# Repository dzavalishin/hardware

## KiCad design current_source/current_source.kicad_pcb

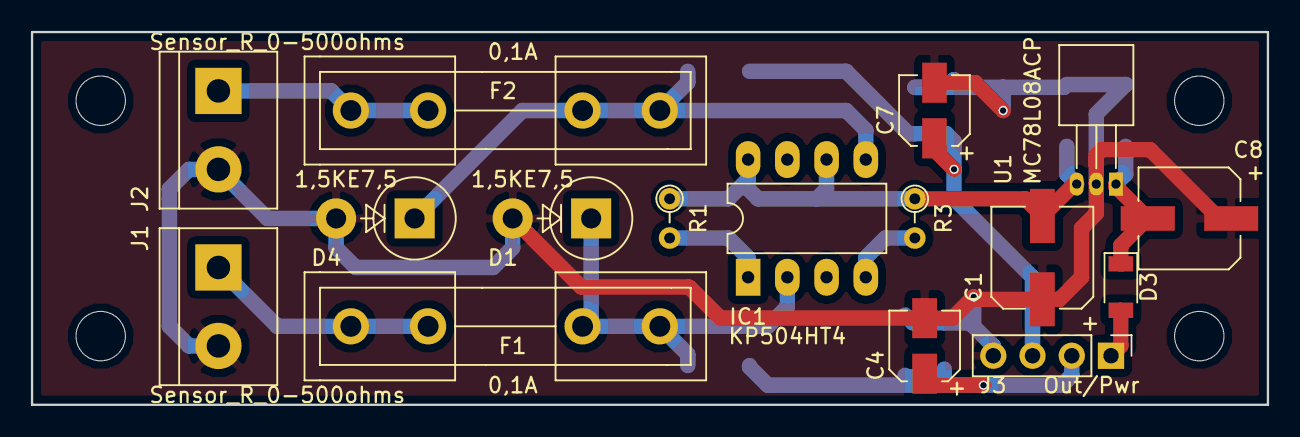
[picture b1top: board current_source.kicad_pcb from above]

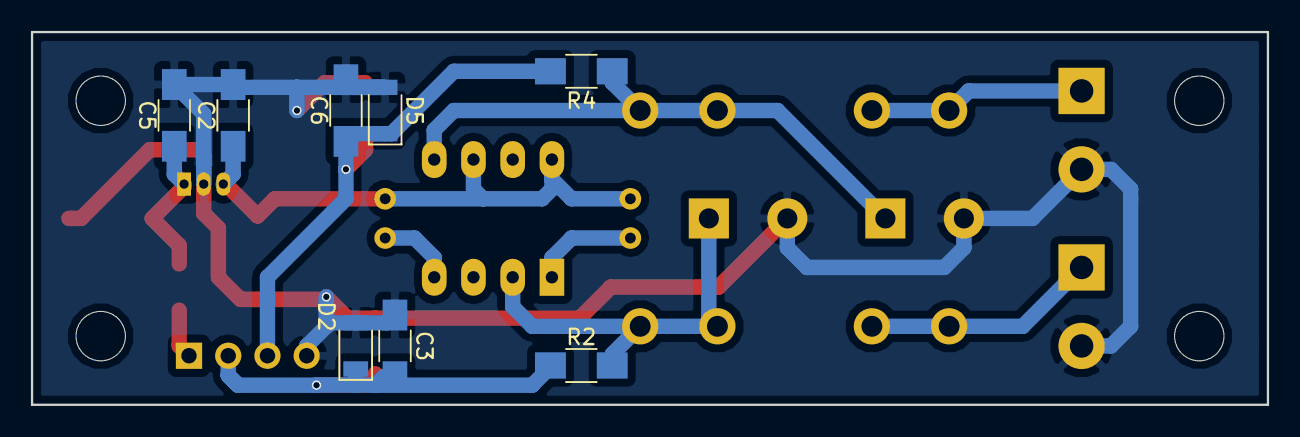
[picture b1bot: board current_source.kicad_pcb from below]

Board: 2 copper layers, 80.0 x 24.1 mm, 24 parts (8 on the bottom side), 12 nets.

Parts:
C1, C8: 100,0; CP_Elec_6.3x5.3
C2, C5: 0,33; C_1206_HandSoldering
C3, C6: 0,1; C_1206_HandSoldering
C4, C7: 10,0; CP_Elec_4x5.7
D1, D4: 1,5KE7,5; D_DO-201_P5.08mm_Vertical_AnodeUp
D2, D5: 4v7; D_1206
D3: 1n4148; D_1206
F1, F2: 0,1A; Fuseholder5x20_horiz_open_inline_Type-I
IC1: КР504НТ4; DIP-8_W7.62mm_LongPads
J1, J2: Sensor_R_0-500ohms; TerminalBlock_bornier-2_P5.08mm
J3: Out/Pwr; Pin_Header_Straight_1x04_Pitch2.54mm
R1, R3: 200 1%; R_Axial_DIN0204_L3.6mm_D1.6mm_P2.54mm_Vertical
R2, R4: 560; R_1206_HandSoldering
U1: MC78L08ACP; TO-92_Horizontal1_Inline_Narrow_Oval

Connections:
+8V: C1.2, C2.1, IC1.6, IC1.8, R1.1, R3.1, U1.3
+12V: D3.2, J3.1
/ADC_In_A: C3.1, C4.1, D2.1, J3.2, R2.1
/ADC_In_B: C6.1, C7.1, D5.1, J3.3, R4.1
GND: C1.1, C2.2, C3.2, C4.2, C5.2, C6.2, C7.2, C8.1, D1.2, D2.2, D4.2, D5.2, J1.2, J2.2, J3.4, U1.2
unnamed: C5.1, C8.2, D3.1, U1.1
unnamed: D1.1, F1.1, IC1.2, R2.2
unnamed: D4.1, F2.1, IC1.5, R4.2
unnamed: F1.2, J1.1
unnamed: F2.2, J2.1
unnamed: IC1.1, R1.2
unnamed: IC1.4, R3.2

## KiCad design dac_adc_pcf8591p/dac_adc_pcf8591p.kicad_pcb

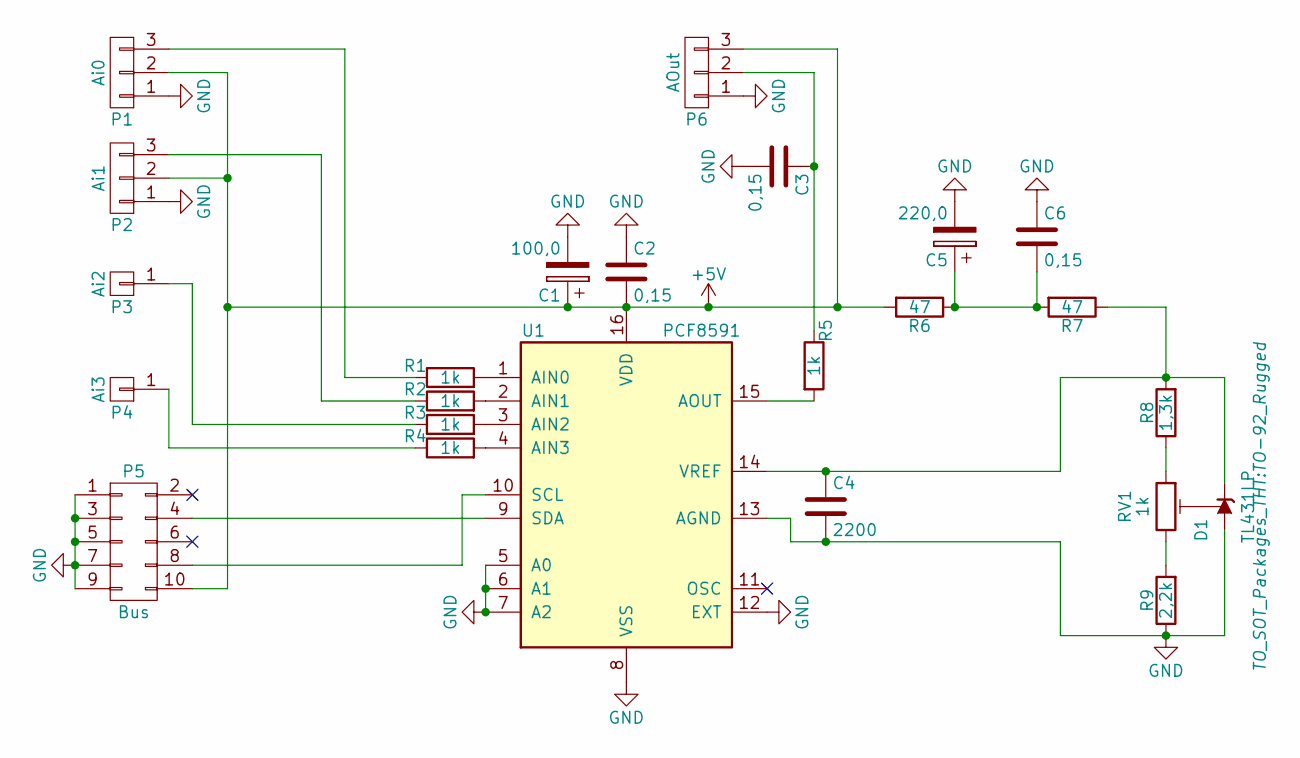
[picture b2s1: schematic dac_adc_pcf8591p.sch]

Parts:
C1: 100,0; CP_Tantalum_Case-B_EIA-3528-21_Hand
C2, C3, C6: 0,15; C_1206_HandSoldering
C4: 2200; C_1206_HandSoldering
C5: 220,0; CP_Tantalum_Case-B_EIA-3528-21_Hand
D1: TL431LP; TO-92_Rugged
P1: Ai0; Pin_Header_Straight_1x03_Pitch2.54mm
P2: Ai1; Pin_Header_Straight_1x03_Pitch2.54mm
P3: Ai2; Pin_Header_Straight_1x01_Pitch2.54mm
P4: Ai3; Pin_Header_Straight_1x01_Pitch2.54mm
P5: Bus; Pin_Header_Straight_2x05_Pitch2.54mm
P6: AOut; Pin_Header_Straight_1x03_Pitch2.54mm
R1, R2, R3, R4, R5: 1k; R_1206_HandSoldering
R6, R7: 47; R_1206_HandSoldering
R8: 1,3k; R_1206_HandSoldering
R9: 2,2k; R_1206_HandSoldering
RV1: 1k; Potentiometer_Trimmer_Bourns_3296W
U1: PCF8591; DIP-16_W7.62mm_LongPads

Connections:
+5V: C1.1, C2.2, P1.2, P2.2, P5.10, P6.3, R6.2, U1.16 (VDD)
GND: C1.2, C2.1, C3.2, C4.2, C5.2, C6.1, D1.2 (A), P1.1, P2.1, P5.1, P5.3, P5.5, P5.7, P5.9, P6.1, R9.1, U1.5 (A0), U1.6 (A1), U1.7 (A2), U1.8 (VSS), U1.12 (EXT), U1.13 (AGND)
unnamed: C3.1, P6.2, R5.1
unnamed: C4.1, D1.3 (K), R7.1, R8.2, U1.14 (VREF)
unnamed: C5.1, C6.2, R6.1, R7.2
unnamed: D1.1 (REF), RV1.2
unnamed: P1.3, R1.1
unnamed: P2.3, R2.1
unnamed: P3.1, R3.1
unnamed: P4.1, R4.1
unnamed: P5.4, U1.9 (SDA)
unnamed: P5.8, U1.10 (SCL)
unnamed: R1.2, U1.1 (AIN0)
unnamed: R2.2, U1.2 (AIN1)
unnamed: R3.2, U1.3 (AIN2)
unnamed: R4.2, U1.4 (AIN3)
unnamed: R5.2, U1.15 (AOUT)
unnamed: R8.1, RV1.1
unnamed: R9.2, RV1.3

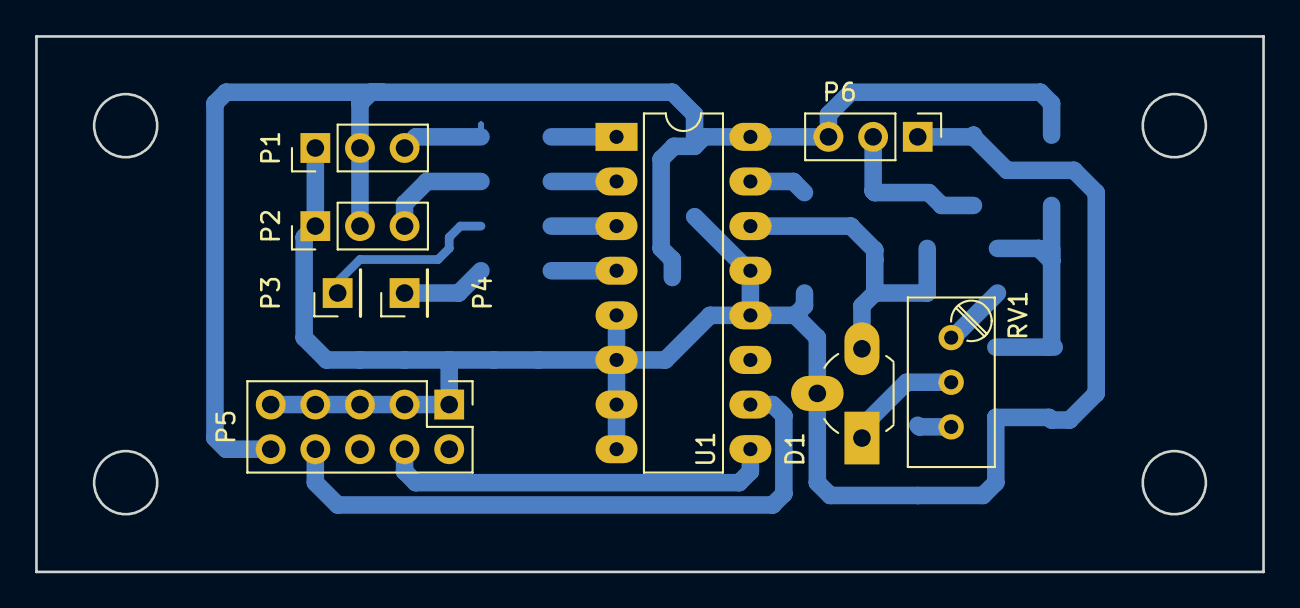
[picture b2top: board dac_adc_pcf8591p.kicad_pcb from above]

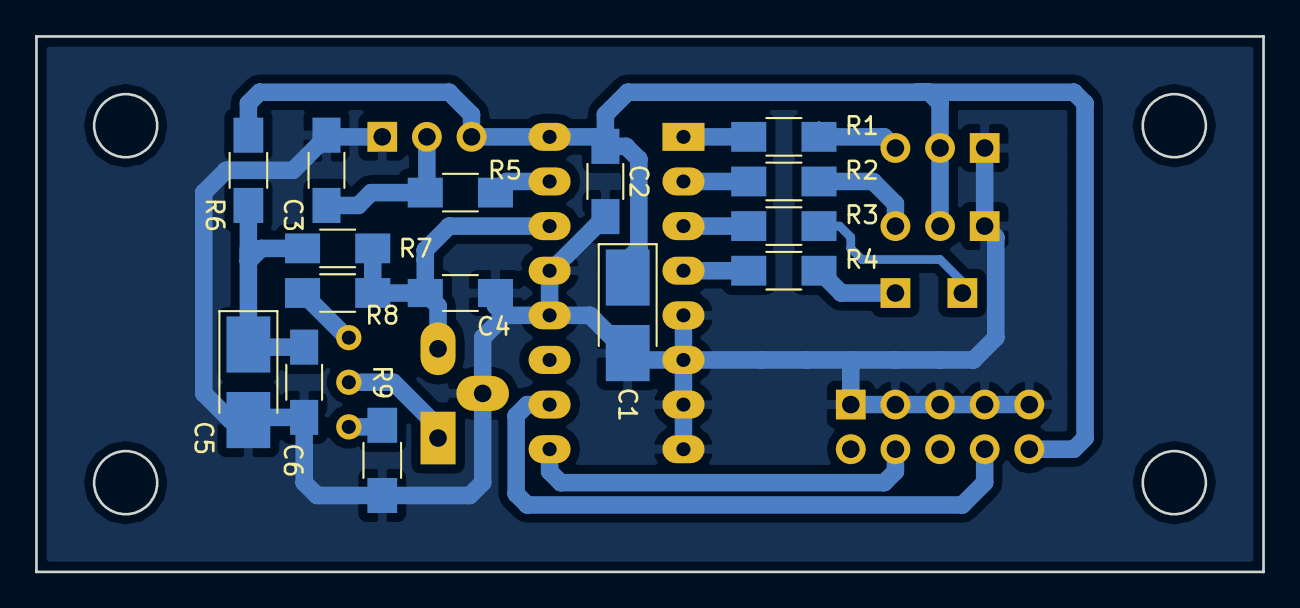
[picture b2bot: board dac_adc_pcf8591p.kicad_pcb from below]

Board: 2 copper layers, 69.9 x 30.5 mm, 24 parts (15 on the bottom side), 19 nets.

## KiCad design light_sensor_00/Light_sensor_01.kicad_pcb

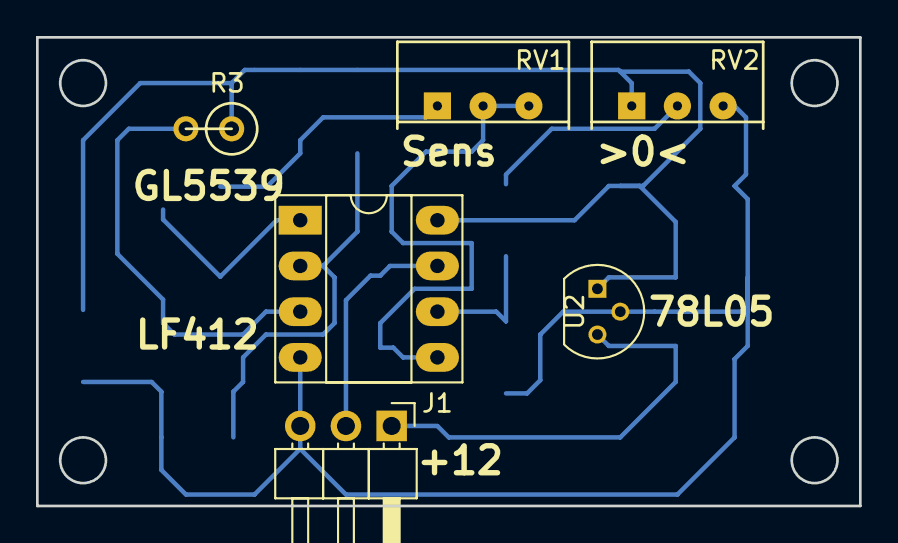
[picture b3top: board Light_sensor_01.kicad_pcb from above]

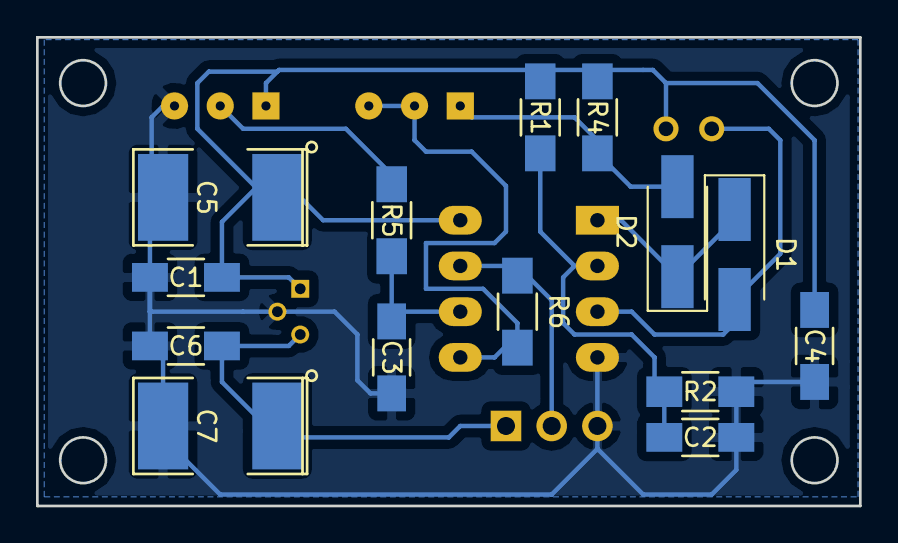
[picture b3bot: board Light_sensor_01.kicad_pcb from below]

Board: 2 copper layers, 45.7 x 26.0 mm, 20 parts (14 on the bottom side), 11 nets.

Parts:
C1, C2, C3, C4, C6: 0,1; C_1206_HandSoldering
C5: 220,0; SMD-2112_Pol
C7: 47,0; SMD-2112_Pol
D1, D2: 1N4148; D_SMA_Handsoldering
J1: Pwr/Out; Pin_Header_Angled_1x03_Pitch2.54mm
R1, R2: 220k; R_1206_HandSoldering
R3: GL5539; R1
R4, R5: 1k; R_1206_HandSoldering
R6: 47k; R_1206_HandSoldering
RV1: 10k; Potentiometer_Trimmer-Suntan-TSR-3386C
RV2: 47k; Potentiometer_Trimmer-Suntan-TSR-3386C
U1: LF412CN; DIP-8_W7.62mm_Socket_LongPads
U2: 78L05; TO-92_Molded_Narrow

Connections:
/+5: C1.2, C4.1, C5.1, R1.1, R3.1, R4.1, RV2.1, U1.8, U2.1
/+12: C6.1, C7.1, J1.1, U2.3
/Bal: C3.1, R5.1, U1.6
/Out: J1.2, R6.1, U1.7
/Ref: C2.1, R1.2, R2.1, U1.2
/Sens: D1.2, R3.2, U1.3
GND: C1.1, C2.2, C3.2, C4.2, C5.2, C6.2, C7.2, J1.3, R2.2, RV2.3, U1.4, U2.2
unnamed: D1.1, D2.1, U1.1
unnamed: D2.2, R4.2, RV1.1
unnamed: R5.2, RV2.2
unnamed: R6.2, RV1.2, RV1.3, U1.5

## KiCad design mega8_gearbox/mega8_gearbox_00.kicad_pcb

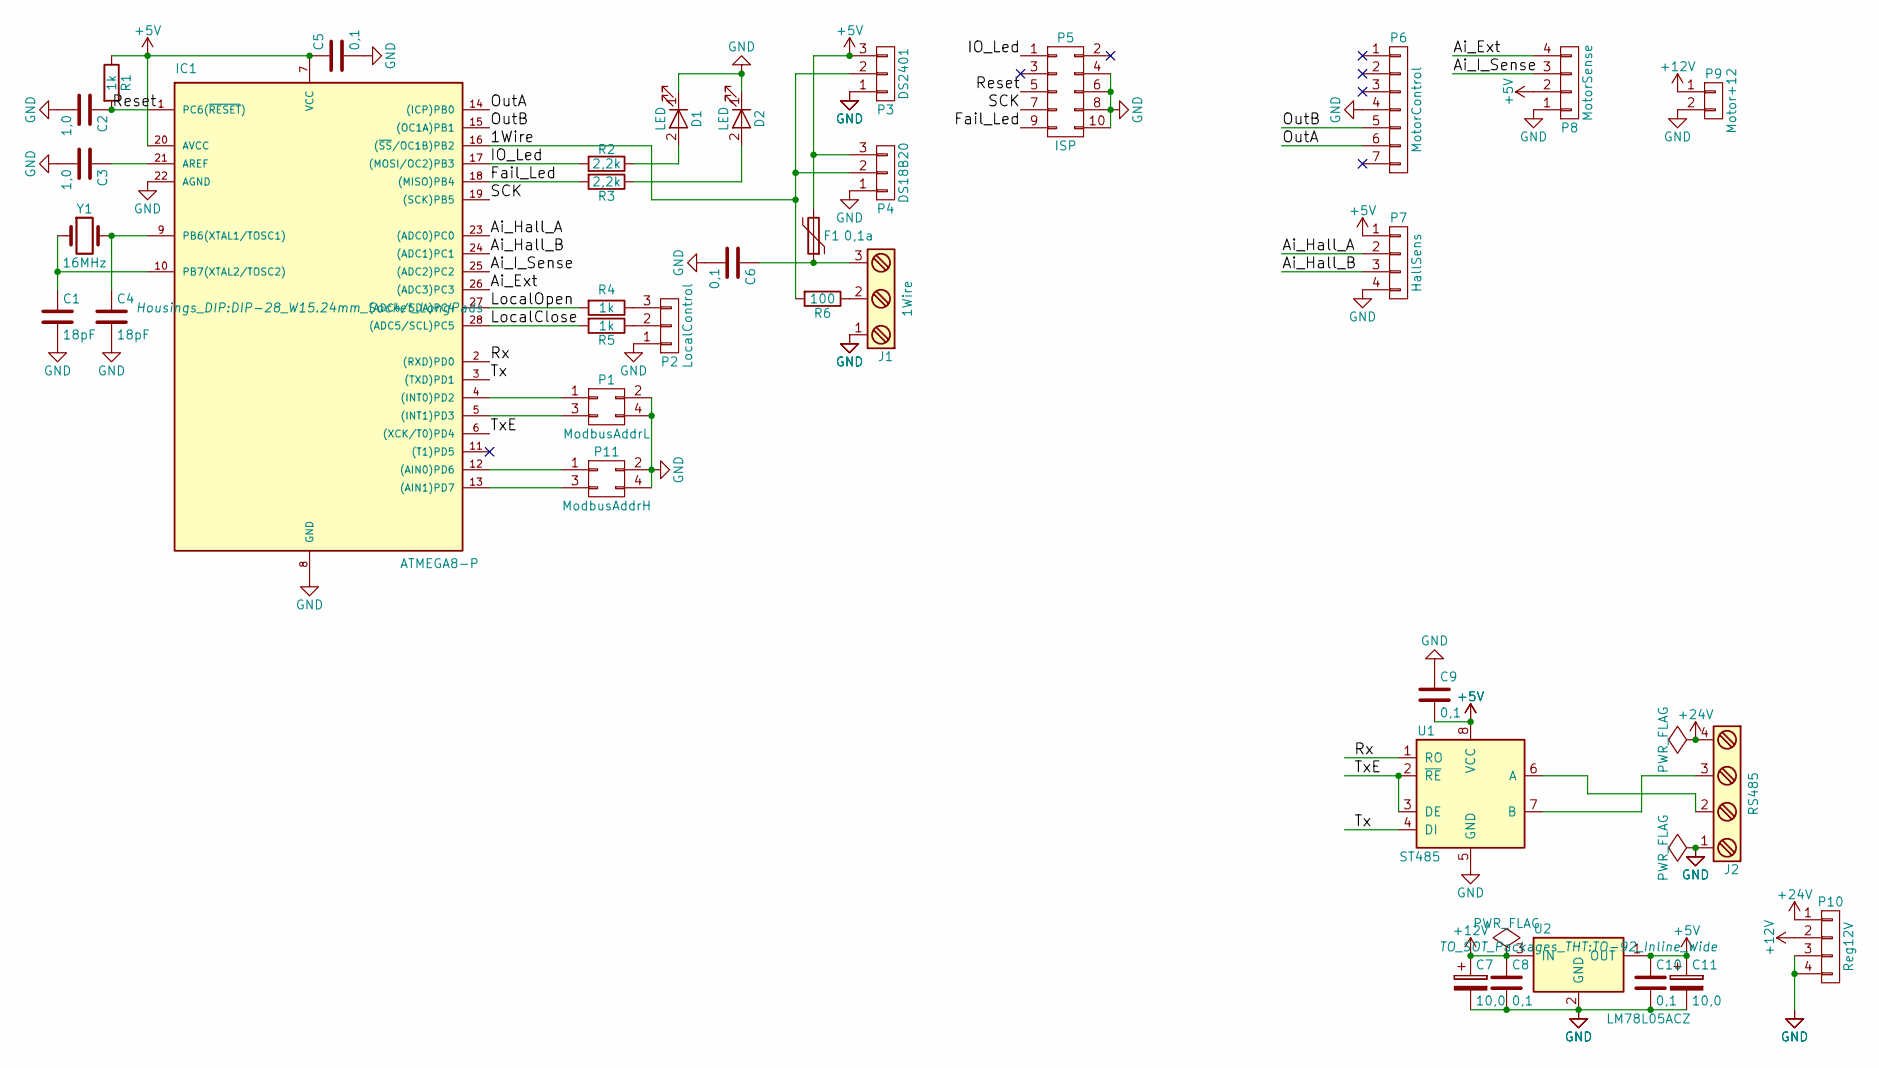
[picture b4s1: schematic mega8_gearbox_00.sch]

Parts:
C1, C4: 18pF; C_1206_HandSoldering
C2, C3: 1,0; C_1206_HandSoldering
C5, C6, C8, C9, C10: 0,1; C_1206_HandSoldering
C7, C11: 10,0; SMD-1206_Pol
D1, D2: LED; LED_D3.0mm
F1: 0,1a; R_Box_L8.4mm_W2.5mm_P5.08mm
IC1: ATMEGA8-P; DIP-28_W15.24mm_Socket_LongPads
J1: 1Wire; TerminalBlock_Pheonix_MKDS1.5-3pol
J2: RS485; TerminalBlock_Pheonix_MKDS1.5-4pol
P1: ModbusAddrL; Socket_Strip_Straight_2x02
P2: LocalControl; Socket_Strip_Straight_1x03
P3: DS2401; Socket_Strip_Straight_1x03
P4: DS18B20; Socket_Strip_Straight_1x03
P5: ISP; Socket_Strip_Straight_2x05
P6: MotorControl; Socket_Strip_Straight_1x07
P7: HallSens; Socket_Strip_Straight_1x04
P8: MotorSense; Socket_Strip_Straight_1x04
P9: Motor+12; Socket_Strip_Straight_1x02
P10: Reg12V; Socket_Strip_Straight_1x04
P11: ModbusAddrH; Socket_Strip_Straight_2x02
R1, R4, R5: 1k; R_1206_HandSoldering
R2, R3: 2,2k; R_1206_HandSoldering
R6: 100; R_Axial_DIN0204_L3.6mm_D1.6mm_P5.08mm_Horizontal
U1: ST485; DIP-8_W7.62mm_Socket_LongPads
U2: LM78L05ACZ; TO-92_Inline_Wide
Y1: 16MHz; Crystal_HC49-U_Vertical

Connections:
+5V: C5.1, C9.2, C10.1, C11.1, F1.2, IC1.7 (VCC), IC1.20 (AVCC), P3.3, P4.3, P7.1, P8.2, R1.1, U1.8 (VCC), U2.1 (OUT)
+12V: C7.1, C8.1, P9.1, P10.2, U2.3 (IN)
+24V: J2.4, P10.1
/1Wire: IC1.16 ((~SS~/OC1B)PB2), P3.2, P4.2, R6.2
/Ai_Ext: IC1.26 ((ADC3)PC3), P8.4
/Ai_Hall_A: IC1.23 ((ADC0)PC0), P7.2
/Ai_Hall_B: IC1.24 ((ADC1)PC1), P7.3
/Ai_I_Sense: IC1.25 ((ADC2)PC2), P8.3
/Fail_Led: IC1.18 ((MISO)PB4), P5.9, R3.2
/IO_Led: IC1.17 ((MOSI/OC2)PB3), P5.1, R2.2
/LocalClose: IC1.28 ((ADC5/SCL)PC5), R5.2
/LocalOpen: IC1.27 ((ADC4/SDA)PC4), R4.2
/OutA: IC1.14 ((ICP)PB0), P6.6
/OutB: IC1.15 ((OC1A)PB1), P6.5
/Reset: C2.1, IC1.1 (PC6(~RESET~)), P5.5, R1.2
/Rx: IC1.2 ((RXD)PD0), U1.1 (RO)
/SCK: IC1.19 ((SCK)PB5), P5.7
/Tx: IC1.3 ((TXD)PD1), U1.4 (DI)
/TxE: IC1.6 ((XCK/T0)PD4), U1.2 (~RE~), U1.3 (DE)
GND: C1.2, C2.2, C3.2, C4.2, C5.2, C6.2, C7.2, C8.2, C9.1, C10.2, C11.2, D1.1 (K), D2.1 (K), IC1.8 (GND), IC1.22 (AGND), J1.1, J2.1, P1.2, P1.4, P2.1, P3.1, P4.1, P5.4, P5.6, P5.8, P5.10, P6.4, P7.4, P8.1, P9.2, P10.3, P10.4, P11.2, P11.4, U1.5 (GND), U2.2 (GND)
unnamed: C1.1, IC1.10 (PB7(XTAL2/TOSC2)), Y1.1
unnamed: C3.1, IC1.21 (AREF)
unnamed: C4.1, IC1.9 (PB6(XTAL1/TOSC1)), Y1.2
unnamed: C6.1, F1.1, J1.3
unnamed: D1.2 (A), R2.1
unnamed: D2.2 (A), R3.1
unnamed: IC1.4 ((INT0)PD2), P1.1
unnamed: IC1.5 ((INT1)PD3), P1.3
unnamed: IC1.12 ((AIN0)PD6), P11.1
unnamed: IC1.13 ((AIN1)PD7), P11.3
unnamed: J1.2, R6.1
unnamed: J2.2, U1.6 (A)
unnamed: J2.3, U1.7 (B)
unnamed: P2.2, R5.1
unnamed: P2.3, R4.1

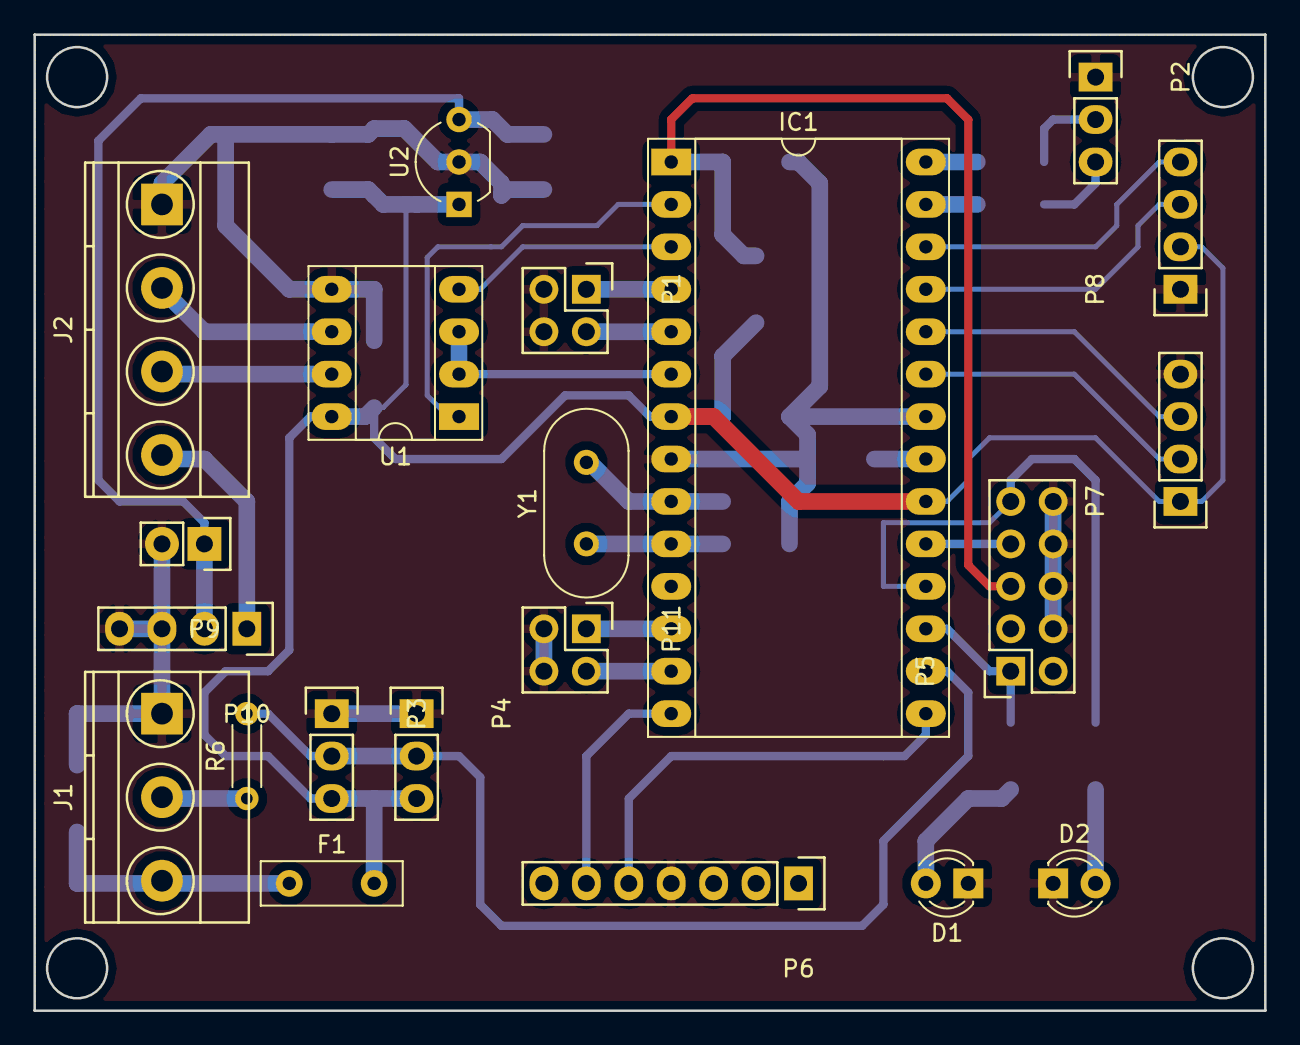
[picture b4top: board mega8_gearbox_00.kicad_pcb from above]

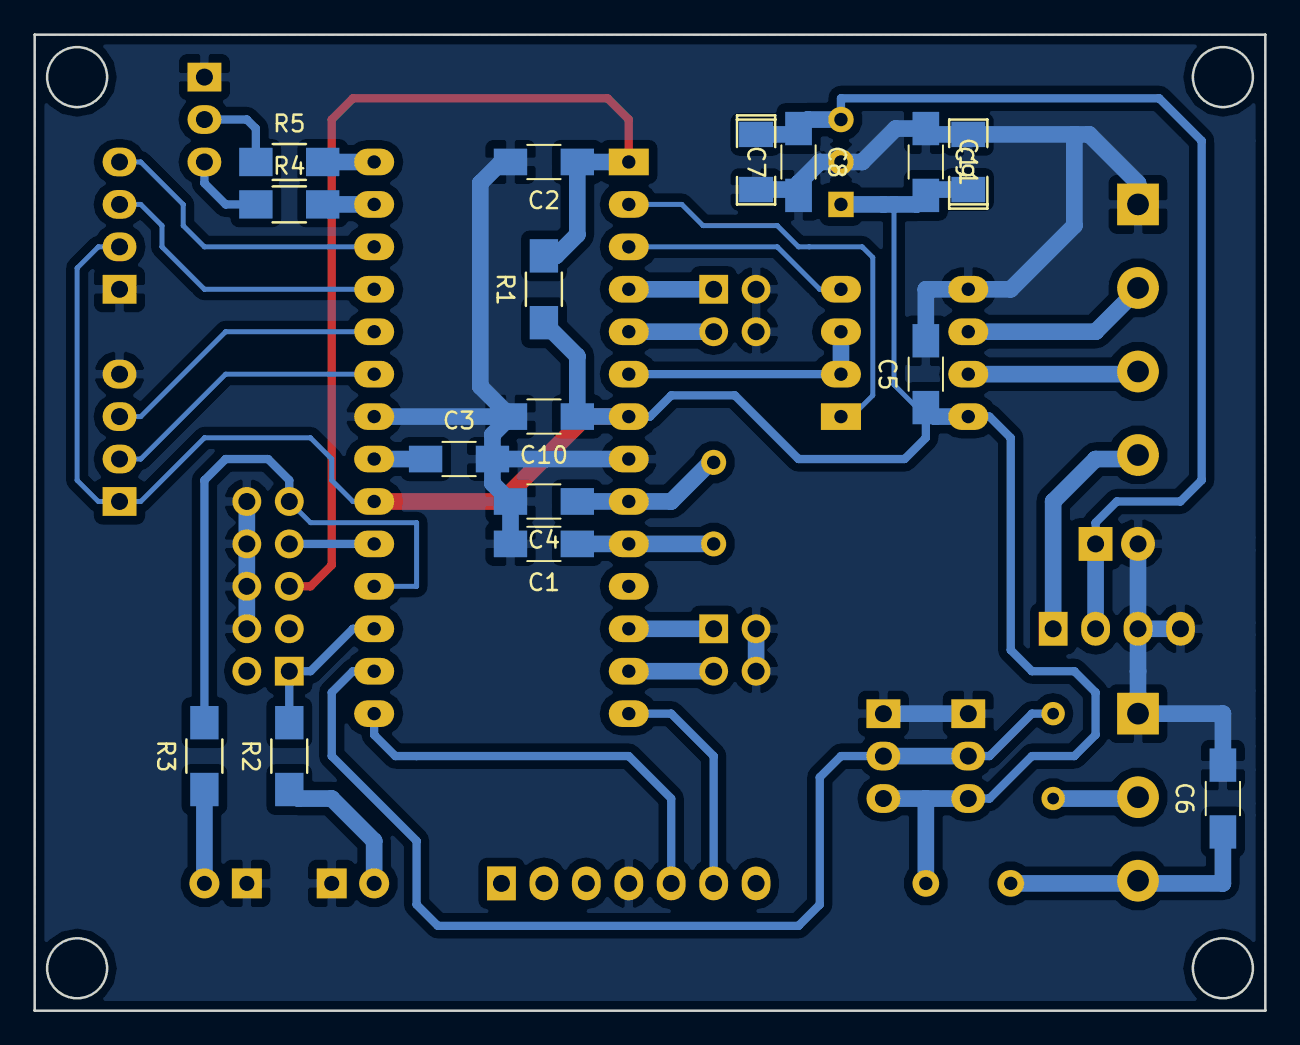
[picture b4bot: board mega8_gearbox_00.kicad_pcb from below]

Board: 2 copper layers, 73.7 x 58.4 mm, 37 parts (16 on the bottom side), 35 nets.

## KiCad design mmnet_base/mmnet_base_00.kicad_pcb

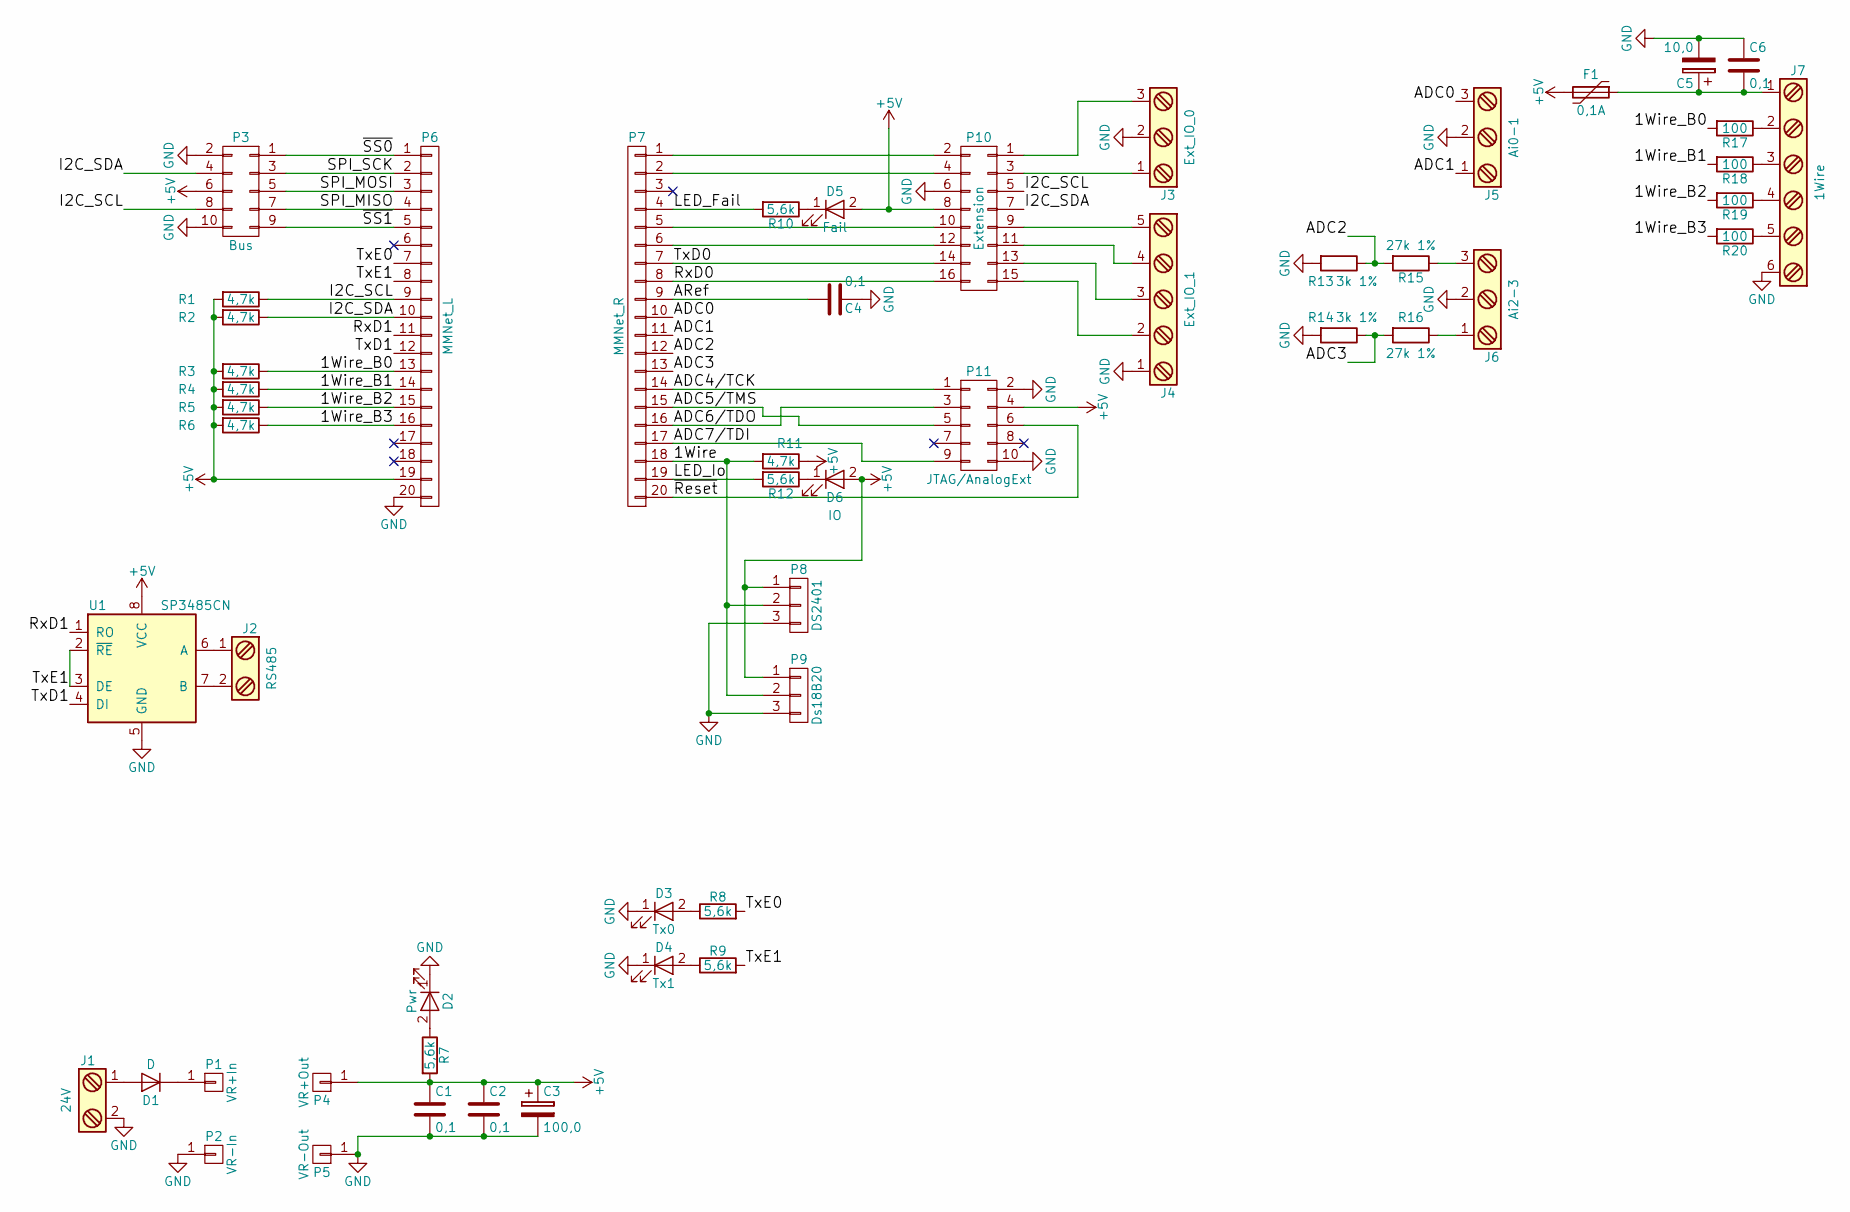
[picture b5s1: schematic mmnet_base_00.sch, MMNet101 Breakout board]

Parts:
C1, C2, C4, C6: 0,1; C_1206_HandSoldering
C3: 100,0; SMD-2512_Pol
C5: 10,0; SMD-2512_Pol
D1: D; D_MELF_Handsoldering
D2: Pwr; LED_D3.0mm
D3: Tx0; LED_D3.0mm
D4: Tx1; LED_D3.0mm
D5: Fail; LED_D3.0mm
D6: IO; LED_D3.0mm
F1: 0,1A; SMD-1206_Pol
J1: 24V; TerminalBlock_Pheonix_MPT-2.54mm_2pol
J2: RS485; TerminalBlock_Pheonix_MPT-2.54mm_2pol
J3: Ext_IO_0; TerminalBlock_Pheonix_MPT-2.54mm_3pol
J4: Ext_IO_1; TerminalBlock_Pheonix_MPT-2.54mm_5pol
J5: Ai0-1; TerminalBlock_Pheonix_MPT-2.54mm_3pol
J6: Ai2-3; TerminalBlock_Pheonix_MPT-2.54mm_3pol
J7: 1Wire; TerminalBlock_Pheonix_MPT-2.54mm_6pol
P1: VR+In; Socket_Strip_Straight_1x01
P2: VR-In; Socket_Strip_Straight_1x01
P3: Bus; Socket_Strip_Straight_2x05
P4: VR+Out; Socket_Strip_Straight_1x01
P5: VR-Out; Socket_Strip_Straight_1x01
P6: MMNet_L; Socket_Strip_Straight_1x20
P7: MMNet_R; Socket_Strip_Straight_1x20
P8: DS2401; Socket_Strip_Straight_1x03
P9: Ds18B20; Socket_Strip_Straight_1x03
P10: Extension; Socket_Strip_Straight_2x08
P11: JTAG/AnalogExt; Socket_Strip_Straight_2x05
R1, R2, R3, R4, R5, R6, R11: 4,7k; R_1206_HandSoldering
R7, R8, R9, R10, R12: 5,6k; R_1206_HandSoldering
R13, R14: 3k 1%; R_1206_HandSoldering
R15, R16: 27k 1%; R_1206_HandSoldering
R17, R18, R19, R20: 100; R_1206_HandSoldering
U1: SP3485CN; SOIC-8_3.9x4.9mm_Pitch1.27mm

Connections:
+5V: C1.1, C2.1, C3.1, D5.2 (A), D6.2 (A), F1.2, P3.6, P4.1, P6.19, P8.1, P9.1, P10.8, P11.4, R1.2, R2.2, R3.2, R4.2, R5.2, R6.2, R7.2, R11.1, U1.8 (VCC)
/1Wire: P7.18, P8.2, P9.2, R11.2
/1Wire_B0: P6.13, R3.1, R17.2
/1Wire_B1: P6.14, R4.1, R18.2
/1Wire_B2: P6.15, R5.1, R19.2
/1Wire_B3: P6.16, R6.1, R20.2
/ADC0: J5.3, P7.10
/ADC1: J5.1, P7.11
/ADC2: P7.12, R13.1, R15.2
/ADC3: P7.13, R14.1, R16.2
/ADC4/TCK: P7.14, P11.1
/ADC5/TMS: P7.15, P11.5
/ADC6/TDO: P7.16, P11.3
/ADC7/TDI: P7.17, P11.9
/ARef: C4.2, P7.9
/I2C_SCL: P3.8, P6.9, P10.5, R1.1
/I2C_SDA: P3.4, P6.10, P10.7, R2.1
/LED_Fail: P7.4, R10.2
/LED_Io: P7.19, R12.2
/RxD0: P7.8, P10.16
/RxD1: P6.11, U1.1 (RO)
/SPI_MISO: P3.7, P6.4
/SPI_MOSI: P3.5, P6.3
/SPI_SCK: P3.3, P6.2
/TxD0: P7.7, P10.14
/TxD1: P6.12, U1.4 (DI)
/TxE0: P6.7, R8.2
/TxE1: P6.8, R9.2, U1.2 (~RE~), U1.3 (DE)
/~Reset: P7.20, P11.6
/~SS0: P3.1, P6.1
/~SS1: P3.9, P6.5
GND: C1.2, C2.2, C3.2, C4.1, C5.2, C6.1, D2.1 (K), D3.1 (K), D4.1 (K), J1.2, J3.2, J4.1, J5.2, J6.2, J7.6, P2.1, P3.2, P3.10, P5.1, P6.20, P8.3, P9.3, P10.6, P11.2, P11.10, R13.2, R14.2, U1.5 (GND)
unnamed: C5.1, C6.2, F1.1, J7.1
unnamed: D1.1 (K), P1.1
unnamed: D1.2 (A), J1.1
unnamed: D2.2 (A), R7.1
unnamed: D3.2 (A), R8.1
unnamed: D4.2 (A), R9.1
unnamed: D5.1 (K), R10.1
unnamed: D6.1 (K), R12.1
unnamed: J2.1, U1.6 (A)
unnamed: J2.2, U1.7 (B)
unnamed: J3.1, P10.3
unnamed: J3.3, P10.1
unnamed: J4.2, P10.15
unnamed: J4.3, P10.13
unnamed: J4.4, P10.11
unnamed: J4.5, P10.9
unnamed: J6.1, R16.1
unnamed: J6.3, R15.1
unnamed: J7.2, R17.1
unnamed: J7.3, R18.1
unnamed: J7.4, R19.1
unnamed: J7.5, R20.1
unnamed: P7.1, P10.2
unnamed: P7.2, P10.4
unnamed: P7.5, P10.10
unnamed: P7.6, P10.12

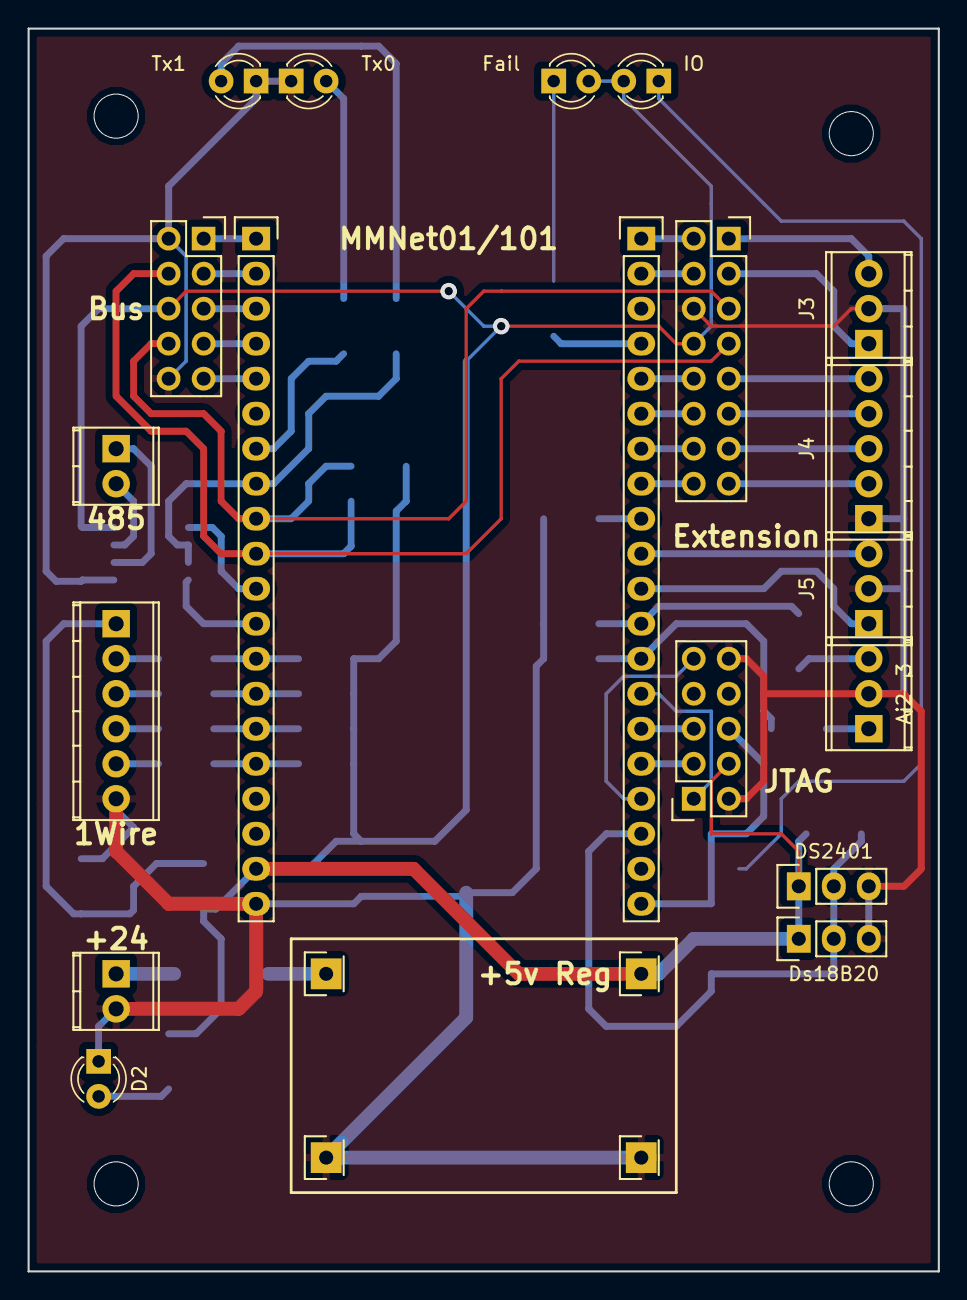
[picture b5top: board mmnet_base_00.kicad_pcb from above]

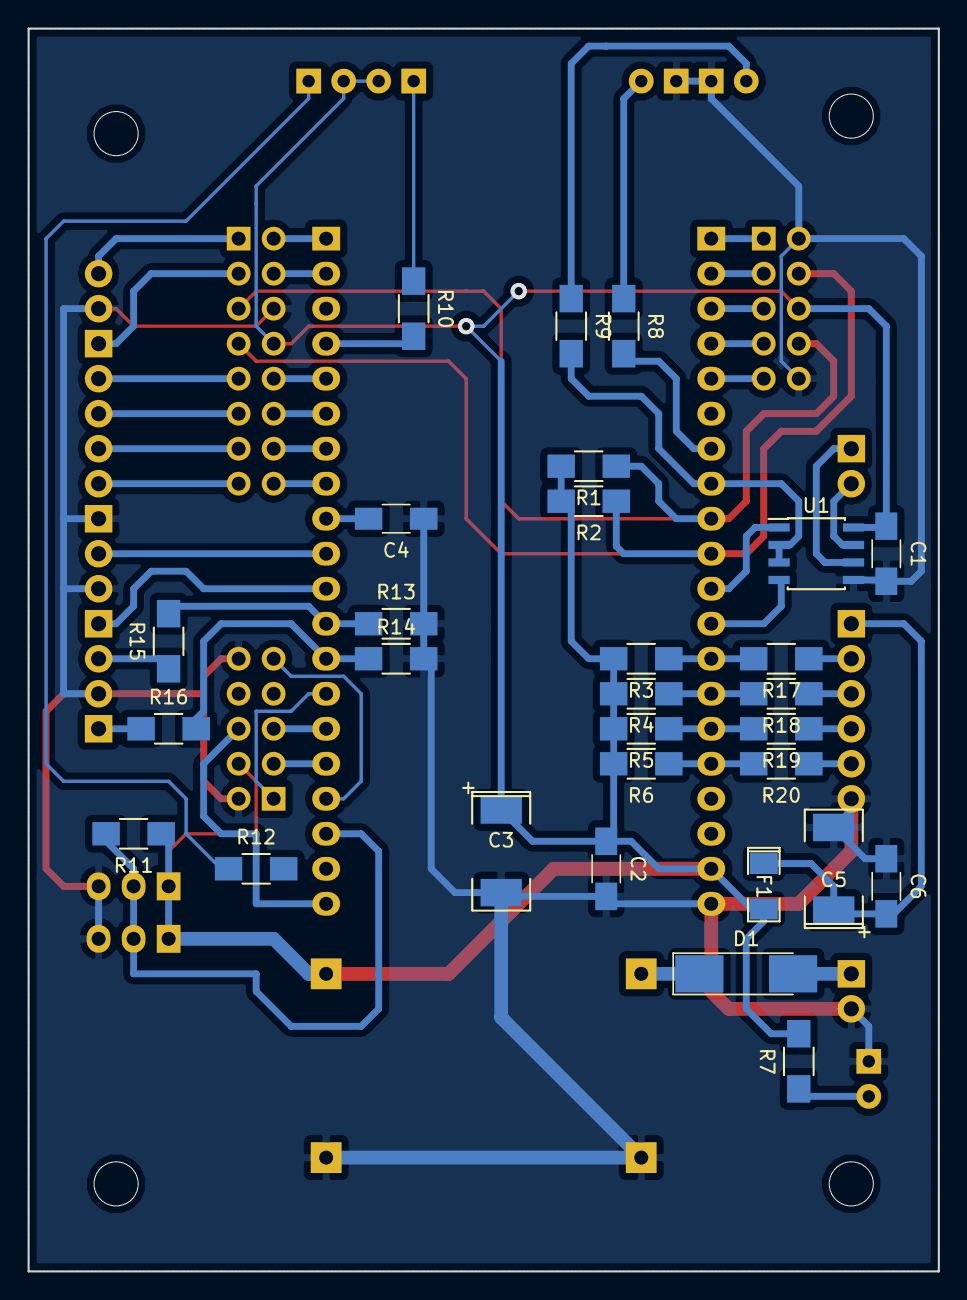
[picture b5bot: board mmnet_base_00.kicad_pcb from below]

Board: 2 copper layers, 66.0 x 90.2 mm, 52 parts (29 on the bottom side), 58 nets.

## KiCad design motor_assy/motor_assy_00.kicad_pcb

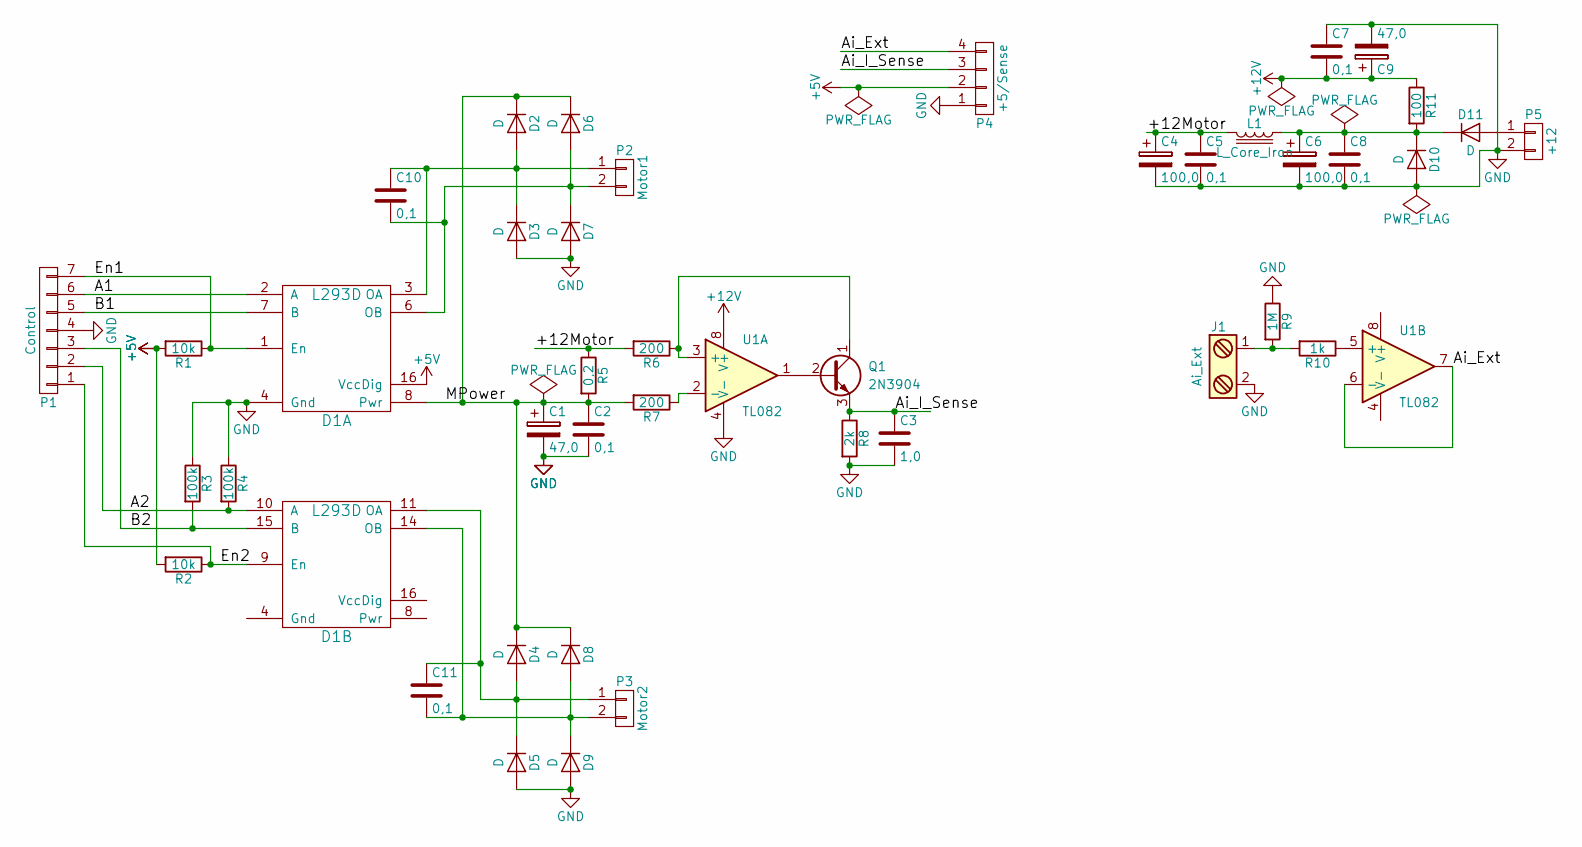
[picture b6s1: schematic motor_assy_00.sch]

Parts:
C1, C9: 47,0; SMD-2112_Pol
C2, C5, C7, C8, C10, C11: 0,1; C_1206_HandSoldering
C3: 1,0; C_1206_HandSoldering
C4, C6: 100,0; SMD-2112_Pol
D1: L293D; DIP-16_W7.62mm_Socket_LongPads
D2, D3, D4, D5, D6, D7, D8, D9, D10, D11: D; D_MiniMELF_Handsoldering
J1: Ai_Ext; TerminalBlock_Pheonix_MKDS1.5-2pol
L1: L_Core_Iron; Choke_Toroid_8x16mm_Vertical
P1: Control; Socket_Strip_Angled_1x07
P2: Motor1; Socket_Strip_Angled_1x02
P3: Motor2; Socket_Strip_Angled_1x02
P4: +5/Sense; Socket_Strip_Angled_1x04
P5: +12; Socket_Strip_Angled_1x02
Q1: 2N3904; TO-92_Molded_Narrow
R1, R2: 10k; R_1206_HandSoldering
R3, R4: 100k; R_1206_HandSoldering
R5: 0,2; R_Axial_DIN0414_L11.9mm_D4.5mm_P15.24mm_Horizontal
R6, R7: 200; R_1206_HandSoldering
R8: 2k; R_1206_HandSoldering
R9: 1M; R_1206_HandSoldering
R10: 1k; R_1206_HandSoldering
R11: 100; R_1206_HandSoldering
U1: TL082; DIP-8_W7.62mm_Socket_LongPads

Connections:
+5V: D1.16 (VccDig), P4.2, R1.2, R2.2
+12V: C7.2, C9.1, R11.1, U1.8 (V+)
/+12Motor: C4.1, C5.1, L1.2, R5.1, R6.2
/A1: D1.2 (A), P1.6
/A2: D1.10 (A), P1.2, R4.2
/Ai_Ext: P4.4, U1.6 (-), U1.7
/Ai_I_Sense: C3.1, P4.3, Q1.3 (E), R8.1
/B1: D1.7 (B), P1.5
/B2: D1.15 (B), P1.3, R3.2
/En1: D1.1 (En), P1.7, R1.1
/En2: D1.9 (En), P1.1, R2.1
/MPower: C1.1, C2.1, D1.8 (Pwr), D2.1 (K), D4.1 (K), D6.1 (K), D8.1 (K), R5.2, R7.2
GND: C1.2, C2.2, C3.2, C4.2, C5.2, C6.2, C7.1, C8.2, C9.2, D1.4 (Gnd), D1.5 (Gnd), D1.12 (Gnd), D1.13 (Gnd), D3.2 (A), D5.2 (A), D7.2 (A), D9.2 (A), D10.2 (A), J1.2, P1.4, P4.1, P5.2, R3.1, R4.1, R8.2, R9.1, U1.4 (V-)
unnamed: C6.1, C8.1, D10.1 (K), D11.1 (K), L1.1, R11.2
unnamed: C10.1, D1.3 (OA), D2.2 (A), D3.1 (K), P2.1
unnamed: C10.2, D1.6 (OB), D6.2 (A), D7.1 (K), P2.2
unnamed: C11.1, D1.11 (OA), D4.2 (A), D5.1 (K), P3.1
unnamed: C11.2, D1.14 (OB), D8.2 (A), D9.1 (K), P3.2
unnamed: D11.2 (A), P5.1
unnamed: J1.1, R9.2, R10.2
unnamed: Q1.1 (C), R6.1, U1.3 (+)
unnamed: Q1.2 (B), U1.1
unnamed: R7.1, U1.2 (-)
unnamed: R10.1, U1.5 (+)
